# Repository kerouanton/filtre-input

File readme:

Ce projet est destiné à tout radioamateur intéressé dans la construction et la mise au point d'un amplificateur 
à base de triode Russe GS35b.
Il s'agit d'une série de filtres en PI commutés (par le biais d'un étage logique genre Arduino ou simplement à l'aide 
d'un commutateur à galette), et qui dispose par défaut de 10 cellules -une par bande.
Le pcb a été conçu pour pouvoir être coupé dans le sens de sa largeur, 
- soit pour n'installer que 6 filtres correspondant aux 6 bandes WARC "old school" (version traditionnelle du filtre TU6B de WD7S)
voir http://home.earthlink.net/~wd7s/TU-6B.htm
- soit, s'il est coupé par son exact milieu, pour que chaque moitié soit montée en "piggy back" afin de pouvoir loger 
le filtre 10 éléments dans un boitier plus court

Nous recommandons vivement que ce filtre soit installé directement dans le boitier de l'amplificateur
plutôt qu'à l'extérieur. 

Le filtre le plus proche de la triode doit si possible être le filtre de la bande la plus haute (6 mètres ou 10 mètres)
Il est également recommandé de monter la capa shunt de ce filtre directement sur la cathode de la lampe et non à son emplacement prévu
sur le pcb.

Pour plus de renseignements, se reporter au Wiki associé
https://github.com/F6ITU/filtre-input/wiki

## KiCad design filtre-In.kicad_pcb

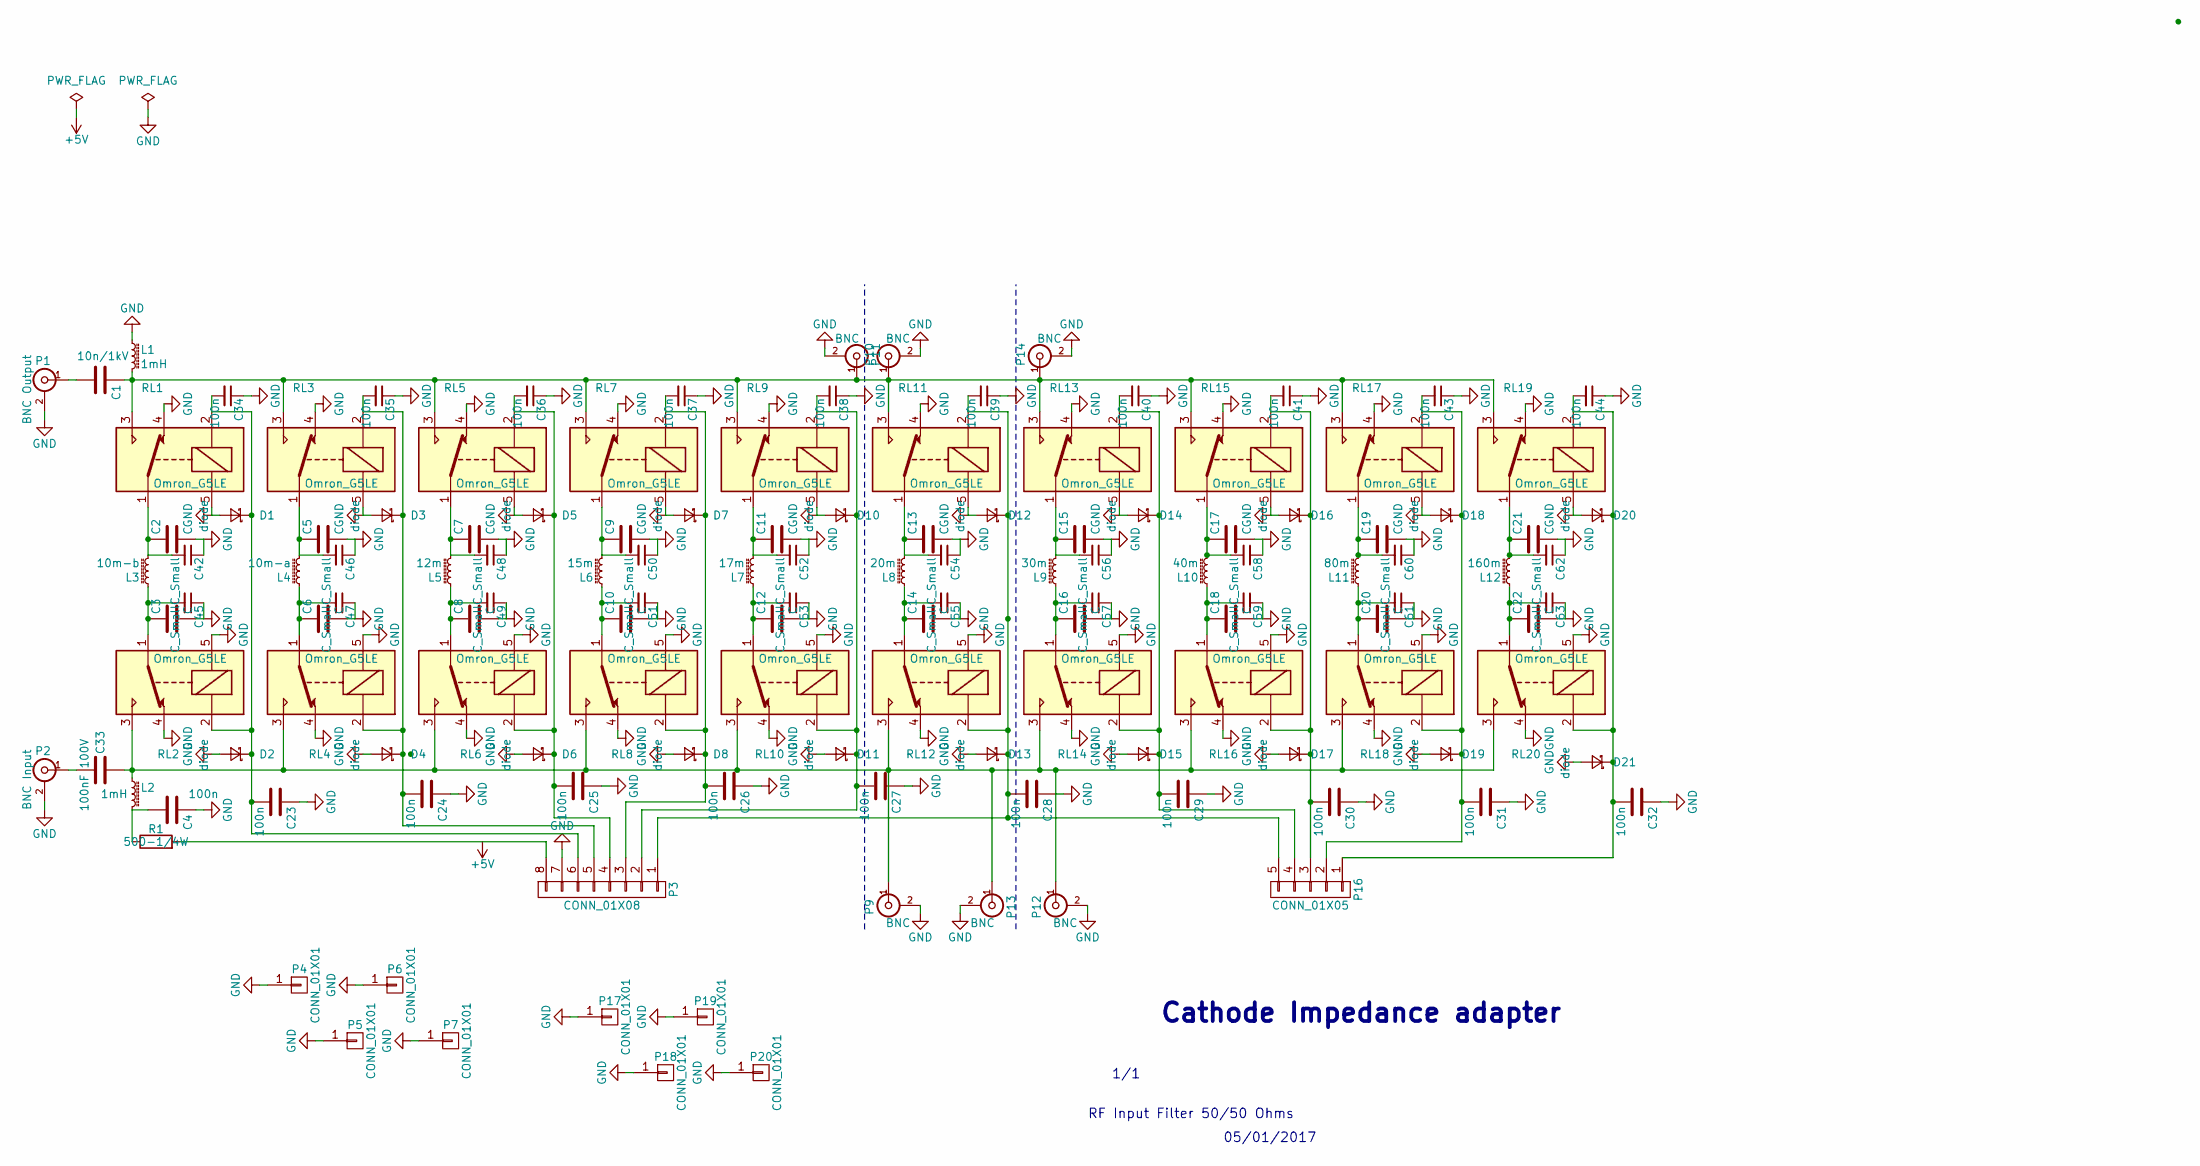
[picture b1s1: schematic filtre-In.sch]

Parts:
C1: 10n/1kV; silver_mica
C2, C3, C5, C6, C7, C8, C9, C10, C11, C12, C13, C14, C15, C16, C17, C18, C19, C20, C21, C22: C; silver_mica
C4, C23, C24, C25, C26, C27, C28, C29, C30, C31, C32, C34, C35, C36, C37, C38, C39, C40, C41, C43, C44: 100n; C_1206_HandSoldering
C33: 100nF 100V; C_1206_HandSoldering
C42, C45, C46, C47, C48, C49, C50, C51, C52, C53, C54, C55, C56, C57, C58, C59, C60, C61, C62, C63: C_Small; C_1825_HandSoldering
D1, D2, D3, D4, D5, D6, D7, D8, D10, D11, D12, D13, D14, D15, D16, D17, D18, D19, D20, D21: diode; D_SMB_Handsoldering
L1, L2: 1mH; Wurt_1mH
L3: 10m-b; T60_80_V
L4: 10m-a; T60_80_V
L5: 12m; T60_80_V
L6: 15m; T60_80_V
L7: 17m; T60_80_V
L8: 20m; T60_80_V
L9: 30m; T60_80_V
L10: 40m; T60_80_V
L11: 80m; T60_80_V
L12: 160m; T60_80_V
P1: BNC Output; coax_2mm
P2: BNC Input; coax_2mm
P3: CONN_01X08; kk100_22-23-2081
P4, P5, P6, P7, P17, P18, P19, P20: CONN_01X01; 1pin
P9, P10, P11, P12, P13, P14: BNC; coax_2mm
P16: CONN_01X05; kk100_22-23-2051
R1: 500-1/4W; R_Axial_DIN0411_L9.9mm_D3.6mm_P12.70mm_Horizontal
RL1, RL2, RL3, RL4, RL5, RL6, RL7, RL8, RL9, RL10, RL11, RL12, RL13, RL14, RL15, RL16, RL17, RL18, RL19, RL20: Omron_G5LE

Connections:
GND: C2.2, C3.2, C4.1, C5.2, C6.2, C7.2, C8.2, C9.2, C10.2, C11.2, C12.2, C13.2, C14.2, C15.2, C16.2, C17.2, C18.2, C19.2, C20.2, C21.2, C22.2, C23.1, C24.1, C25.1, C26.1, C27.1, C28.1, C29.1, C30.1, C31.1, C32.1, C34.1, C35.1, C36.1, C37.1, C38.1, C39.1, C40.1, C41.1, C42.1, C43.1, C44.1, C45.1, C46.1, C47.1, C48.1, C49.1, C50.1, C51.1, C52.1, C53.1, C54.1, C55.1, C56.1, C57.1, C58.1, C59.1, C60.1, C61.1, C62.1, C63.1, D1.2 (A), D2.2 (A), D3.2 (A), D4.2 (A), D5.2 (A), D6.2 (A), D7.2 (A), D8.2 (A), D10.2 (A), D11.2 (A), D12.2 (A), D13.2 (A), D14.2 (A), D15.2 (A), D16.2 (A), D17.2 (A), D18.2 (A), D19.2 (A), D20.2 (A), D21.2 (A), L1.1, P1.2 (Ext), P2.2 (Ext), P3.7, P4.1, P5.1, P6.1, P7.1, P9.2 (Ext), P10.2 (Ext), P11.2 (Ext), P12.2 (Ext), P13.2 (Ext), P14.2 (Ext), P17.1, P18.1, P19.1, P20.1, RL1.4, RL1.5, RL2.4, RL2.5, RL3.4, RL3.5, RL4.4, RL4.5, RL5.4, RL5.5, RL6.4, RL6.5, RL7.4, RL7.5, RL8.4, RL8.5, RL9.4, RL9.5, RL10.4, RL10.5, RL11.4, RL11.5, RL12.4, RL12.5, RL13.4, RL13.5, RL14.4, RL14.5, RL15.4, RL15.5, RL16.4, RL16.5, RL17.4, RL17.5, RL18.4, RL18.5, RL19.4, RL19.5, RL20.4, RL20.5
unnamed: C1.1, L1.2, P10.1 (In), P11.1 (In), P14.1 (In), RL1.3, RL3.3, RL5.3, RL7.3, RL9.3, RL11.3, RL13.3, RL15.3, RL17.3, RL19.3
unnamed: C1.2, P1.1 (In)
unnamed: C2.1, C42.2, L3.2, RL1.1
unnamed: C3.1, C45.2, L3.1, RL2.1
unnamed: C4.2, L2.2, R1.1
unnamed: C10.1, C51.2, L6.1, RL8.1
unnamed: C11.1, C52.2, L7.2, RL9.1
unnamed: C12.1, C53.2, L7.1, RL10.1
unnamed: C13.1, C54.2, L8.2, RL11.1
unnamed: C14.1, C55.2, L8.1, RL12.1
unnamed: C15.1, C56.2, L9.2, RL13.1
unnamed: C16.1, C57.2, L9.1, RL14.1
unnamed: C17.1, C58.2, L10.2, RL15.1
unnamed: C18.1, C59.2, L10.1, RL16.1
unnamed: C19.1, C60.2, L11.2, RL17.1
unnamed: C20.1, C61.2, L11.1, RL18.1
unnamed: C21.1, C62.2, L12.2, RL19.1
unnamed: C22.1, C63.2, L12.1, RL20.1
unnamed: C23.2, C34.2, D1.1 (K), D2.1 (K), P3.6, RL1.2, RL2.2
unnamed: C24.2, C35.2, D3.1 (K), D4.1 (K), P3.5, RL3.2, RL4.2
unnamed: C25.2, C36.2, D5.1 (K), D6.1 (K), P3.4, RL5.2, RL6.2
unnamed: C26.2, C37.2, D7.1 (K), D8.1 (K), P3.3, RL7.2, RL8.2
unnamed: C27.2, C38.2, D10.1 (K), D11.1 (K), P3.2, RL9.2, RL10.2
unnamed: C28.2, C39.2, D12.1 (K), D13.1 (K), P3.1, P16.5, RL11.2, RL12.2
unnamed: C29.2, C40.2, D14.1 (K), D15.1 (K), P16.4, RL13.2, RL14.2
unnamed: C30.2, C41.2, D16.1 (K), D17.1 (K), P16.3, RL15.2, RL16.2
unnamed: C31.2, C43.2, D18.1 (K), D19.1 (K), P16.2, RL17.2, RL18.2
unnamed: C32.2, C44.2, D20.1 (K), D21.1 (K), P16.1, RL19.2, RL20.2
unnamed: C33.1, L2.1, P9.1 (In), P12.1 (In), P13.1 (In), RL2.3, RL4.3, RL6.3, RL8.3, RL10.3, RL12.3, RL14.3, RL16.3, RL18.3, RL20.3
unnamed: C33.2, P2.1 (In)
unnamed: C5.1, C46.2, L4.2, RL3.1
unnamed: C6.1, C47.2, L4.1, RL4.1
unnamed: C7.1, C48.2, L5.2, RL5.1
unnamed: C8.1, C49.2, L5.1, RL6.1
unnamed: C9.1, C50.2, L6.2, RL7.1
unnamed: P3.8, R1.2

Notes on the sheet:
RF Input Filter 50/50 Ohms
1/1
05/01/2017
Cathode Impedance adapter

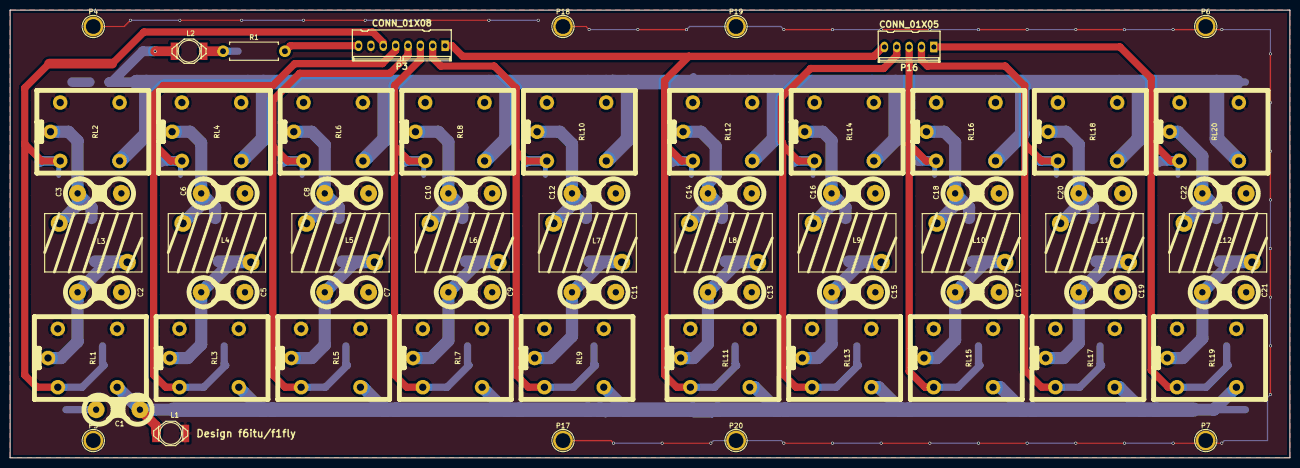
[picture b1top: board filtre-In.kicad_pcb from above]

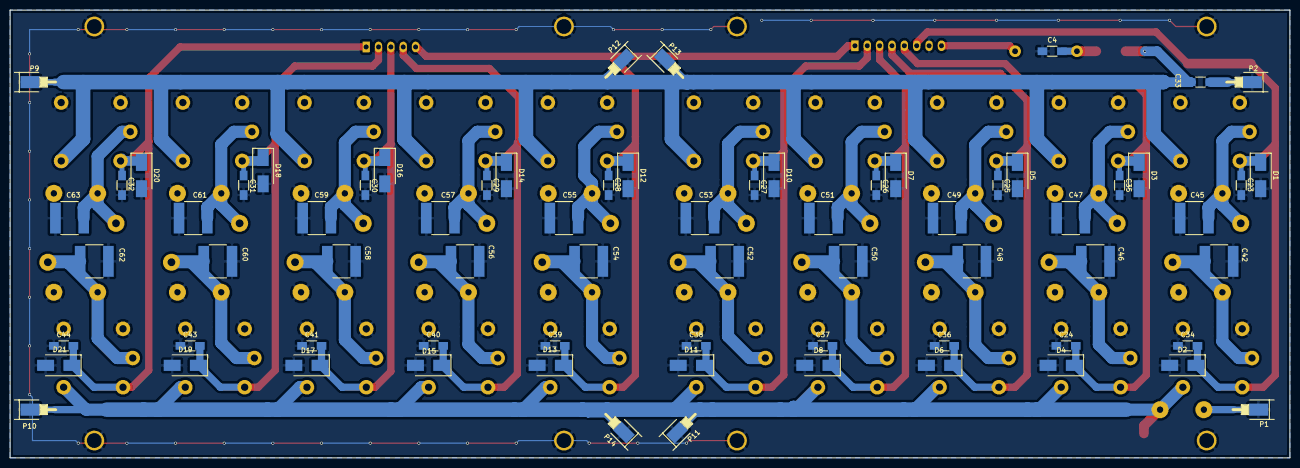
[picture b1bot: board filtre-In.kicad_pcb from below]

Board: 2 copper layers, 263.0 x 92.0 mm, 134 parts (70 on the bottom side), 37 nets.

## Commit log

2017-01-20 filtre input premier jet
2017-01-20 ajout du readme
2017-01-21 version avec formes 3D, sans condos ATC
2017-01-22 version CAO finale, a priori bonne pour la prod
2017-01-31 add new footprint/module
2017-01-31 ajout du wiki dans le readme
2017-02-01 ajout gerber, modif bias
2017-05-02 version finale gravee
2017-06-12 release from June 12 2017, debugged and checked
2017-08-11 changed relay pinout, changed ATC-B footprint
2018-01-13 Fixed encoding to unicode
2018-01-13 removed zap
